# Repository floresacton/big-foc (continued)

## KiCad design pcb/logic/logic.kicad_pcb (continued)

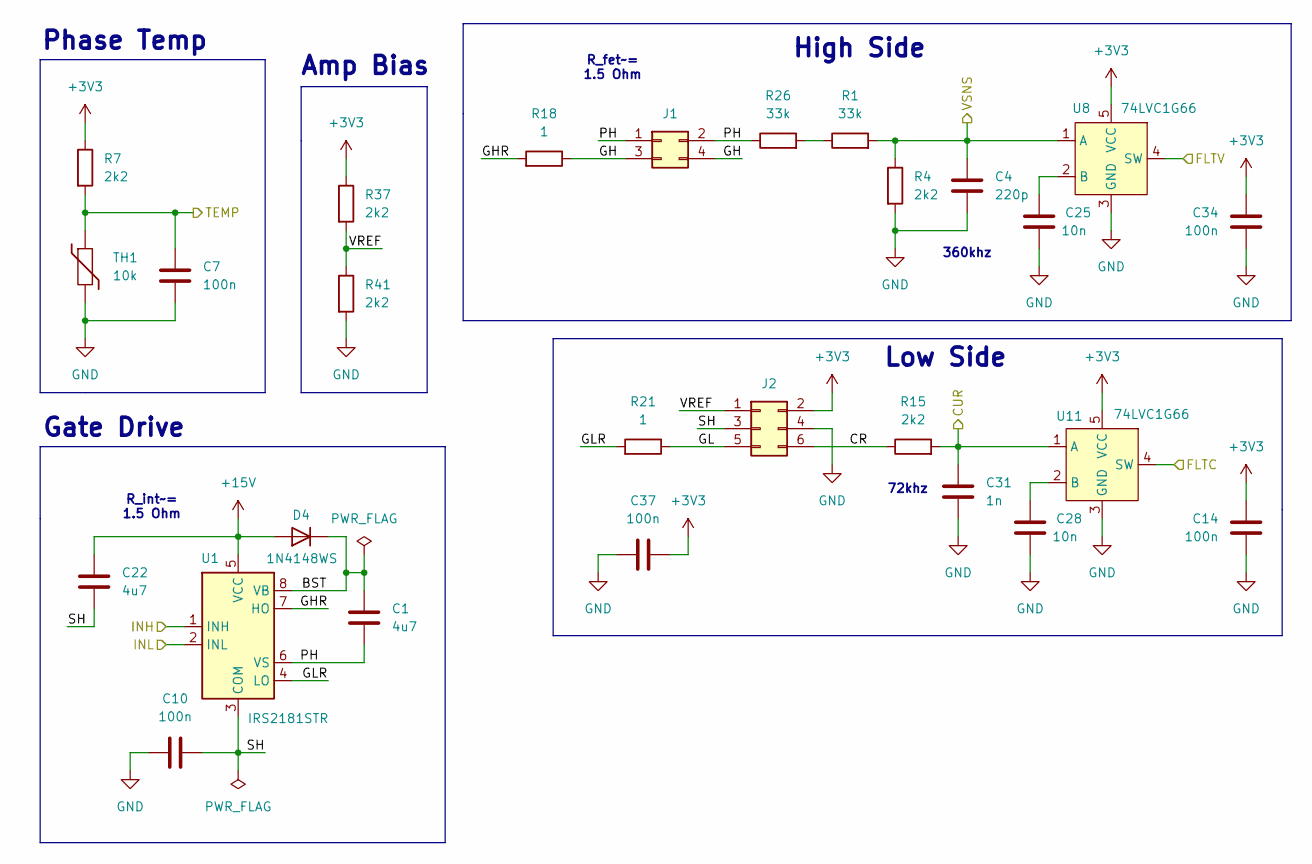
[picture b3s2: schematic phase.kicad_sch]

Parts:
C1: 4u7; C_1206_3216Metric; LCSC C29823
C4: 220p; C_0402_1005Metric; LCSC C1530
C7, C10, C14, C34, C37: 100n; C_0402_1005Metric; LCSC C307331
C22: 4u7; C_0805_2012Metric; LCSC C33546011
C25, C28: 10n; C_0402_1005Metric; LCSC C15195
C31: 1n; C_0402_1005Metric; LCSC C1523
D4: 1N4148WS; D_SOD-323; LCSC C2128
J1: Conn_02x02_Odd_Even; PinSocket_2x02_P1.27mm_Vertical_SMD; LCSC C30607465
J2: Conn_02x03_Odd_Even; PinSocket_2x03_P1.27mm_Vertical_SMD; LCSC C32713074
R1, R26: 33k; R_0402_1005Metric; LCSC C25779
R4, R7, R15, R37, R41: 2k2; R_0402_1005Metric; LCSC C25879
R18, R21: 1; R_0603_1608Metric; LCSC C22936
TH1: 10k; R_0402_1005Metric; LCSC C41417281
U1: IRS2181STR; JEITA_SOIC-8_3.9x4.9mm_P1.27mm; LCSC C20623180
U8, U11: 74LVC1G66; SOT-23-5; LCSC C46553572

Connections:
+3V3: C14.1, C34.1, C37.2, J2.2, R7.1, R37.1, U8.5 (VCC), U11.5 (VCC); also elsewhere on the board
+15V: C22.1, D4.2 (A), U1.5 (VCC); also elsewhere on the board
/ACUR: C31.1, R15.2, U11.1 (A); also elsewhere on the board
/AINH: U1.1 (INH); also elsewhere on the board
/AINL: U1.2 (INL); also elsewhere on the board
/ASNS: C4.1, R1.2, R4.1, U8.1 (A); also elsewhere on the board
/ATEMP: C7.1, R7.2, TH1.1; also elsewhere on the board
/FLTC: U11.4 (SW); also elsewhere on the board
/FLTV: U8.4 (SW); also elsewhere on the board
/Phase1/BST: C1.1, D4.1 (K), U1.8 (VB)
/Phase1/CR: J2.6, R15.1
/Phase1/GH: J1.3, J1.4, R18.1
/Phase1/GHR: R18.2, U1.7 (HO)
/Phase1/GL: J2.5, R21.1
/Phase1/GLR: R21.2, U1.4 (LO)
/Phase1/PH: C1.2, J1.1, J1.2, R26.1, U1.6 (VS)
/Phase1/SH: C10.2, C22.2, J2.3, U1.3 (COM)
/Phase1/VREF: J2.1, R37.2, R41.1
GND: C4.2, C7.2, C10.1, C14.2, C25.2, C28.2, C31.2, C34.2, C37.1, J2.4, R4.2, R41.2, TH1.2, U8.3 (GND), U11.3 (GND); also elsewhere on the board
unnamed: R1.1, R26.2
unnamed: C25.1, U8.2 (B)
unnamed: C28.1, U11.2 (B)

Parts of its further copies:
C2, C3: 4u7; C_1206_3216Metric; LCSC C29823
C5, C6: 220p; C_0402_1005Metric; LCSC C1530
C8, C9, C11, C12, C15, C16, C35, C36, C38, C39: 100n; C_0402_1005Metric; LCSC C307331
C23, C24: 4u7; C_0805_2012Metric; LCSC C33546011
C26, C27, C29, C30: 10n; C_0402_1005Metric; LCSC C15195
C32, C33: 1n; C_0402_1005Metric; LCSC C1523
D5, D6: 1N4148WS; D_SOD-323; LCSC C2128
J3, J5: Conn_02x02_Odd_Even; PinSocket_2x02_P1.27mm_Vertical_SMD; LCSC C30607465
J4, J6: Conn_02x03_Odd_Even; PinSocket_2x03_P1.27mm_Vertical_SMD; LCSC C32713074
R2, R3, R27, R28: 33k; R_0402_1005Metric; LCSC C25779
R5, R6, R8, R9, R16, R17, R38, R40, R42, R43: 2k2; R_0402_1005Metric; LCSC C25879
R19, R20, R22, R23: 1; R_0603_1608Metric; LCSC C22936
TH2, TH3: 10k; R_0402_1005Metric; LCSC C41417281
U2, U3: IRS2181STR; JEITA_SOIC-8_3.9x4.9mm_P1.27mm; LCSC C20623180
U9, U10, U12, U13: 74LVC1G66; SOT-23-5; LCSC C46553572

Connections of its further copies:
+3V3: C15.1, C16.1, C35.1, C36.1, C38.2, C39.2, J4.2, J6.2, R8.1, R9.1, R38.1, R40.1, U9.5 (VCC), U10.5 (VCC), U12.5 (VCC), U13.5 (VCC); also elsewhere on the board
+15V: C23.1, C24.1, D5.2 (A), D6.2 (A), U2.5 (VCC), U3.5 (VCC); also elsewhere on the board
/BCUR: C32.1, R16.2, U12.1 (A); also elsewhere on the board
/BINH: U2.1 (INH); also elsewhere on the board
/BINL: U2.2 (INL); also elsewhere on the board
/BSNS: C5.1, R2.2, R5.1, U9.1 (A); also elsewhere on the board
/BTEMP: C8.1, R8.2, TH2.1; also elsewhere on the board
/CCUR: C33.1, R17.2, U13.1 (A); also elsewhere on the board
/CINH: U3.1 (INH); also elsewhere on the board
/CINL: U3.2 (INL); also elsewhere on the board
/CSNS: C6.1, R3.2, R6.1, U10.1 (A); also elsewhere on the board
/CTEMP: C9.1, R9.2, TH3.1; also elsewhere on the board
/FLTC: U12.4 (SW), U13.4 (SW); also elsewhere on the board
/FLTV: U9.4 (SW), U10.4 (SW); also elsewhere on the board
/Phase2/BST: C2.1, D5.1 (K), U2.8 (VB)
/Phase2/CR: J4.6, R16.1
/Phase2/GH: J3.3, J3.4, R19.1
/Phase2/GHR: R19.2, U2.7 (HO)
/Phase2/GL: J4.5, R22.1
/Phase2/GLR: R22.2, U2.4 (LO)
/Phase2/PH: C2.2, J3.1, J3.2, R27.1, U2.6 (VS)
/Phase2/SH: C11.2, C23.2, J4.3, U2.3 (COM)
/Phase2/VREF: J4.1, R38.2, R42.1
/Phase3/BST: C3.1, D6.1 (K), U3.8 (VB)
/Phase3/CR: J6.6, R17.1
/Phase3/GH: J5.3, J5.4, R20.1
/Phase3/GHR: R20.2, U3.7 (HO)
/Phase3/GL: J6.5, R23.1
/Phase3/GLR: R23.2, U3.4 (LO)
/Phase3/PH: C3.2, J5.1, J5.2, R28.1, U3.6 (VS)
/Phase3/SH: C12.2, C24.2, J6.3, U3.3 (COM)
/Phase3/VREF: J6.1, R40.2, R43.1
GND: C5.2, C6.2, C8.2, C9.2, C11.1, C12.1, C15.2, C16.2, C26.2, C27.2, C29.2, C30.2, C32.2, C33.2, C35.2, C36.2, C38.1, C39.1, J4.4, J6.4, R5.2, R6.2, R42.2, R43.2, TH2.2, TH3.2, U9.3 (GND), U10.3 (GND), U12.3 (GND), U13.3 (GND); also elsewhere on the board
unnamed: R2.1, R27.2
unnamed: R3.1, R28.2
unnamed: C26.1, U9.2 (B)
unnamed: C27.1, U10.2 (B)
unnamed: C29.1, U12.2 (B)
unnamed: C30.1, U13.2 (B)

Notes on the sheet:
Low Side
R_fet~= 1.5 Ohm
Amp Bias
R_int~= 1.5 Ohm
Gate Drive
Phase Temp
72khz
360khz
High Side

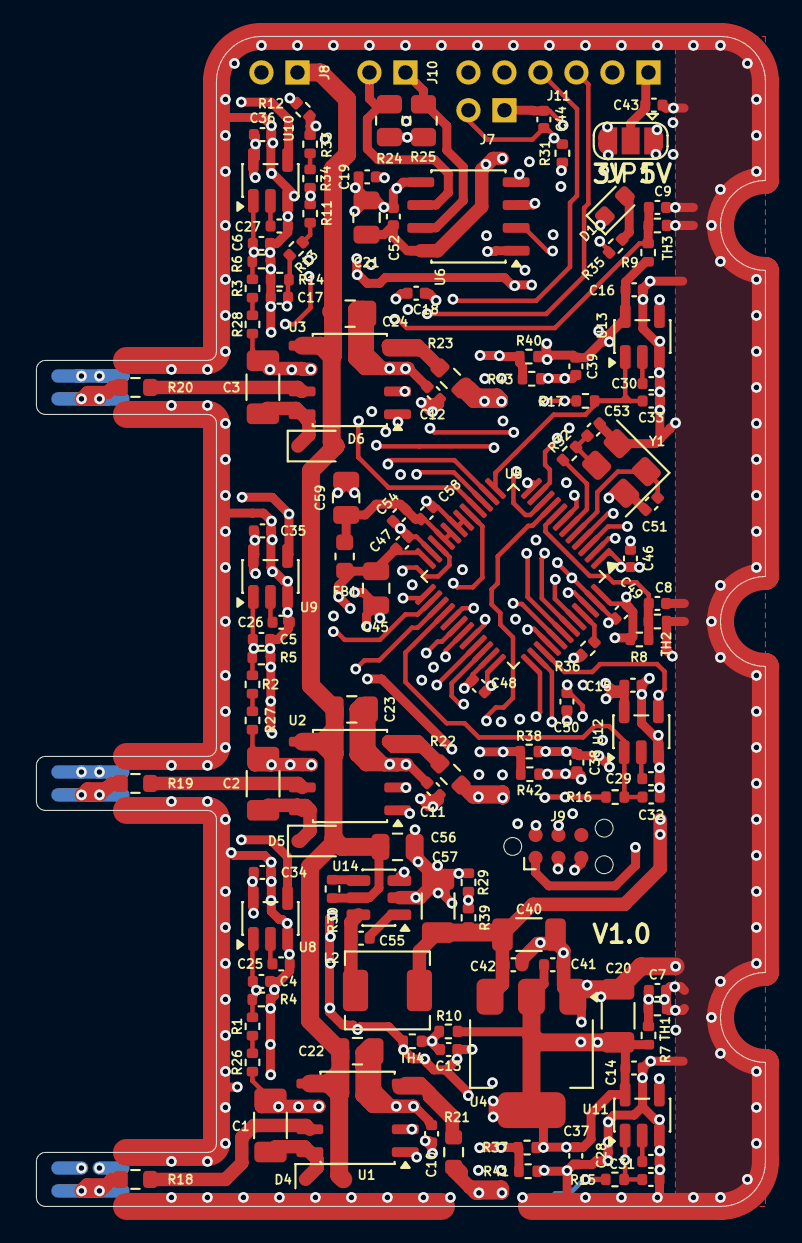
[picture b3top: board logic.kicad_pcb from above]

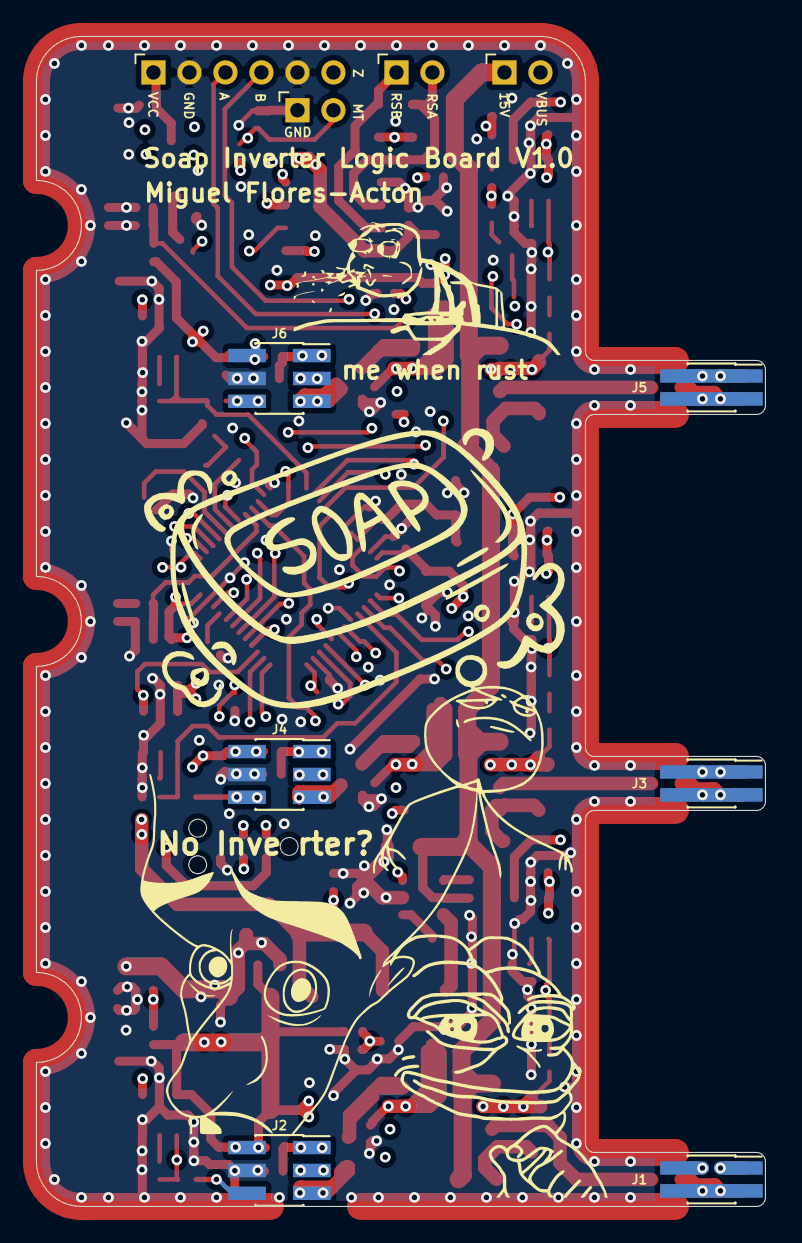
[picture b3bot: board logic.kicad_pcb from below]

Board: 4 copper layers, 40.5 x 65.0 mm, 143 parts (15 on the bottom side), 89 nets.

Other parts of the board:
G1, G2, G3, G4, G5: LOGO

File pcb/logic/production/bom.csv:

Designator,Footprint,Quantity,Value,LCSC Part #
"C1, C2, C3",1206,3,4u7,C29823
"C10, C11, C12, C13, C14, C15, C16, C19, C34, C35, C36, C37, C38, C39, C41, C42, C43, C44, C46, C47, C48, C49, C50, C52, C54, C55, C7, C8, C9",0402,29,100n,C307331
"C17, C4, C5, C6",0402,4,220p,C1530
"C18, C25, C26, C27, C28, C29, C30",0402,7,10n,C15195
"C20, C40, C57",1206,3,22u,C20416445
"C21, C22, C23, C24, C45, C56, C59",0805,7,4u7,C33546011
"C31, C32, C33, C58",0402,4,1n,C1523
"C51, C53",0402,2,10p,C32949
D1,0603,1,LED,C2290
"D4, D5, D6",D_SOD-323,3,1N4148WS,C2128
FB1,0603,1,120,C14709
"J1, J3, J5",PinSocket_2x02_P1.27mm_Vertical_SMD,3,Conn_02x02_Odd_Even,C30607465
"J2, J4, J6",PinSocket_2x03_P1.27mm_Vertical_SMD,3,Conn_02x03_Odd_Even,C32713074
L2,L_TechFuse_SL0420,1,4u7,C22463808
"R1, R11, R13, R2, R26, R27, R28, R3, R30, R33, R34",0402,11,33k,C25779
"R10, R12, R14, R15, R16, R17, R29, R31, R35, R36, R37, R38, R4, R40, R41, R42, R43, R5, R6, R7, R8, R9",0402,22,2k2,C25879
"R18, R19, R20, R21, R22, R23",0603,6,1,C22936
"R24, R25",0805,2,51,C17738
R32,0402,1,330,C25104
R39,0402,1,12k,C25752
"TH1, TH2, TH3, TH4",0402,4,10k,C41417281
"U1, U2, U3",JEITA_SOIC-8_3.9x4.9mm_P1.27mm,3,IRS2181STR,C20623180
"U10, U11, U12, U13, U8, U9",SOT-23-5,6,74LVC1G66,C46553572
U14,SOT-23-6,1,JW5017S,C371172
U4,SOT-223-3_TabPin2,1,AMS1117-3.3,C6186
U5,LQFP-48_7x7mm_P0.5mm,1,STM32G473CBTx,C730111
U6,JEITA_SOIC-8_3.9x4.9mm_P1.27mm,1,SP485E,C6855
Y1,Crystal_SMD_3225-4Pin_3.2x2.5mm,1,16MHz,C13738

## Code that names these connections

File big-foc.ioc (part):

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Mcu.Name=STM32G473C(B-C-E)Tx
Mcu.Package=LQFP48
Mcu.UserName=STM32G473CBTx
PA0.Mode=IN1-Single-Ended
PA0.Signal=ADC1_IN1
PA1.Mode=IN2-Single-Ended
PA1.Signal=ADC1_IN2
PA10.Signal=S_TIM1_CH3
PA11.Mode=PWM Generation1 CH1 CH1N
PA11.Signal=TIM1_CH1N
PA12.Mode=PWM Generation2 CH2 CH2N
PA12.Signal=TIM1_CH2N
PA13.Mode=Serial_Wire
PA13.Signal=SYS_JTMS-SWDIO
PA14.Mode=Serial_Wire
PA14.Signal=SYS_JTCK-SWCLK
PA15.Signal=GPIO_Output
PA2.Mode=IN3-Single-Ended
PA2.Signal=ADC1_IN3
PA3.Mode=IN4-Single-Ended
PA3.Signal=ADC1_IN4
PA4.GPIOParameters=GPIO_Label
PA4.GPIO_Label=GND
PA4.Signal=GPIO_Output
PA5.Mode=IN13-Single-Ended
PA5.Signal=ADC2_IN13
PA6.Mode=IN3-Single-Ended
PA6.Signal=ADC2_IN3
PA7.Mode=INP
PA7.Signal=COMP2_INP
PA8.Signal=S_TIM1_CH1
PA9.Signal=S_TIM1_CH2
PB0.Mode=IN15-Single-Ended
PB0.Signal=ADC1_IN15
PB1.Mode=IN1-Single-Ended
PB1.Signal=ADC3_IN1
PB10.Signal=GPIO_Output
PB11.Mode=IN14-Single-Ended
PB11.Signal=ADC1_IN14
PB12.Mode=IN3-Single-Ended
PB12.Signal=ADC4_IN3
PB13.Mode=IN5-Single-Ended
PB13.Signal=ADC3_IN5
PB14.Mode=IN4-Single-Ended
PB14.Signal=ADC4_IN4
PB15.GPIOParameters=GPIO_Label
PB15.GPIO_Label=GND
PB15.Signal=GPIO_Output
PB2.GPIOParameters=GPIO_Label
PB2.GPIO_Label=GND
PB2.Signal=GPIO_Output
PB3.Signal=S_TIM3_ETR
PB4.Signal=S_TIM3_CH1
PB5.Signal=S_TIM3_CH2
PB6.Mode=Asynchronous
PB6.Signal=USART1_TX
PB7.Mode=Asynchronous
PB7.Signal=USART1_RX
PB9.Mode=PWM Generation3 CH3 CH3N
PB9.Signal=TIM1_CH3N
PC13.Signal=GPIO_Output
PC14-OSC32_IN.Signal=GPIO_Output
PC15-OSC32_OUT.Signal=GPIO_Output
PF0-OSC_IN.Mode=HSE-External-Oscillator
PF0-OSC_IN.Signal=RCC_OSC_IN
PF1-OSC_OUT.Mode=HSE-External-Oscillator
PF1-OSC_OUT.Signal=RCC_OSC_OUT
RCC.HSE_VALUE=8000000
RCC.SYSCLKFreq_VALUE=16000000
board=custom

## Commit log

2025-11-04 Prototype layout
2025-11-07 Test readme format
2025-11-09 Semifinish power and bulk
2025-11-09 Generate step
2025-11-10 Save progress
2025-11-10 Update shunts
2025-11-11 Update calcs
2025-11-13 Add connectors
2025-11-17 Finish rev 1
2025-11-17 Update LICENSE
